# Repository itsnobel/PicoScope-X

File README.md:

# PicoScope-X
**PicoScope-X** is a compact, handheld, lightweight and portable powerful oscilloscope powered by Raspberry Pi Pico 2 (RP2350). It has 4-channel logic analyzer. This build features auto-ranging analog front-end (AFE), real-time power monitoring, a 3.2" TFT display to show outputs in sine waves, rectangles or triangles according to which signal we'll measure. Also onboard micro-SD data logging can help to sort out all data.
## Features

* **Dual-Channel Oscilloscope:** Runs on RB2350's dual core processing power to actively measure the waves formed by buffering sine wave, rectangle or triangle signal like a oscilloscope using high-speed ADCs (ADC0/ADC1). 
* **4-Channel Logic Analyzer:**  Digital signal capture utilizing RP2350 PIO (PIO0) for debugging SPI, I2C, UART, and GPIO states.
* **Auto-Ranging Input (1x / 10x(can be upgraded to 100x):** DG419 analog switches automaticly switch between direct input and a precision resistor divider network for high range voltage measurements.
* **Real-Time Power & Battery Monitor:** Integrated INA219 sensor tracks live current, voltage, and power consumption, and battery capacity (mAh) discharge testing.
* **Interactive UI & Storage:** Dual rotary encoders for seamless menu navigation, timebase/voltage scaling, and a Micro-SD card slot for saving screenshots and waveform data logs.
* **Power Management:** Powered by a 3.7V Li-Po battery with slide-switch control and diode for battery protection and charging while switch is off.

## Photos
The schematic like like mess as There were too many pins
---

---
The PCB designs are kinda cool. Looks like professional design.
---

---

## Repository Structure
PicoScope-X
├── PCB/              # EasyEDA schematic files, PCB layout, and gerbers
├── firmware/         # C++/MicroPython source code for RP2350
├── docs/             # Datasheets, pinout diagrams, and testing logs
└── README.md         # Project documentation

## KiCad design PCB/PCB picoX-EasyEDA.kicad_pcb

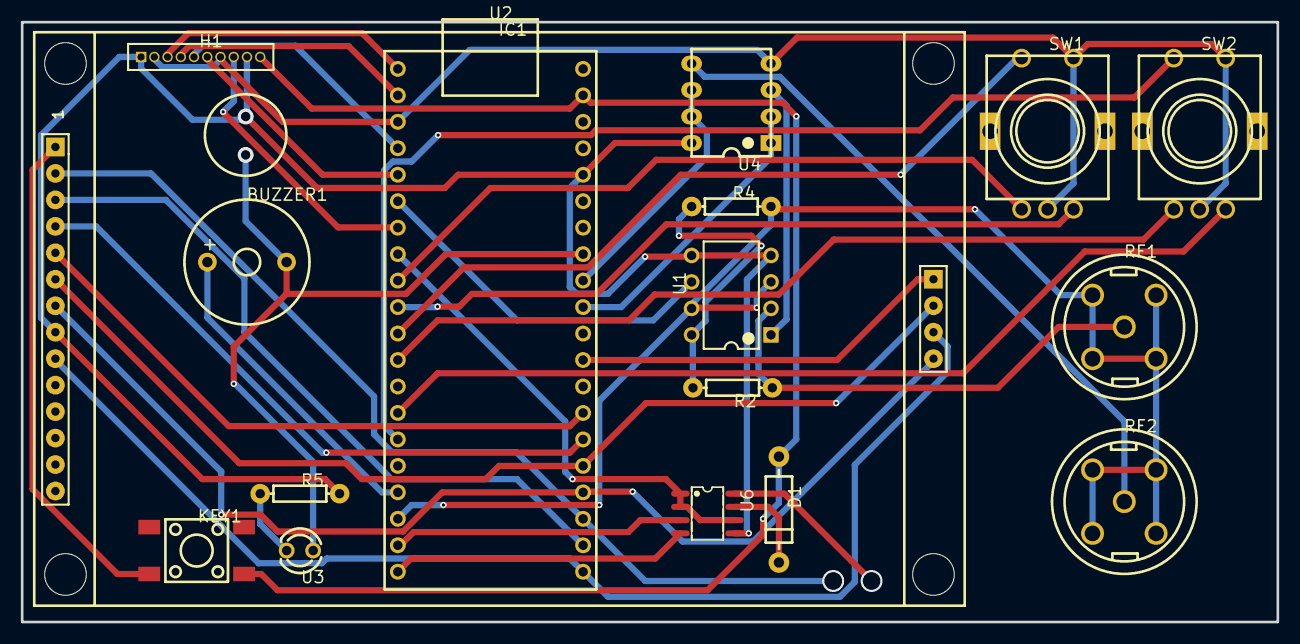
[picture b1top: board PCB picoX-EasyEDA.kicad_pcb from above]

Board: 2 copper layers, 120.5 x 57.6 mm, 17 parts (0 on the bottom side), 38 nets.

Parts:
BUZZER1: BUZZER-12X9; BUZ-TH_BD12.0-P7.60-D0.6-FD
D1: DIODE; DIODE-1N4001
H1: 1.27mm1*10P Straight Headers Pins; HDR-TH_10P-P1.27-V-M-1
IC1: TFT 3.2SPIA; TFT 3.2SPIM
KEY1: PUSHBUTTON; SW-SMD_4P-L6.0-W6.0-P4.50-LS10.0_TL3301EF160QG
R2, R4, R5: 1k; AXIAL-0.3
RF1, RF2: HL2-BNC-JE; BNC-TH_HL2-BNC-JE
SW1, SW2: Rotary switch; SW7-13.75X11.7X6.5MM
U1: DG419; DIP-8_L11.0-W7.6-P2.54-LS7.6-BL
U2: COLOREASYPICO2-RP2350; COMM-TH_COLOREASYPICO2-RP2350
U3: LED-2; LED-TH_BD3.0-P2.54-FD
U4: IC BAN TL072; TL072
U6: INA219BID; SOIC-8_L4.9-W3.9-P1.27-LS6.0-BL

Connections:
IC1_1: IC1.1, KEY1.3
U1_1: U1.1, U4.3
U1_2: R2.1, RF1.5, U1.2
U1_4: H1.1, H1.9, IC1.8, R5.2, U1.4, U1.5, U2.36, U4.8, U6.5
U1_6: U1.6, U2.6
U1_7: R4.2, RF1.1, RF1.2, RF1.3, RF1.4, RF2.1, RF2.2, RF2.3, RF2.4, U1.3, U1.7, U2.18
U1_8: R2.2, R4.1, U1.8
U2_1: H1.3, U2.1
U2_2: H1.4, U2.2
U2_3: H1.2, H1.7, SW1.2, SW1.4, SW2.2, SW2.4, U2.3, U4.4
U2_4: H1.5, U2.4
U2_5: H1.6, U2.5
U2_7: H1.8, U2.7
U2_8: U2.8, U6.1, U6.2, U6.6
U2_9: SW1.1, U2.9
U2_10: SW1.3, U2.10
U2_11: SW1.5, U2.11
U2_12: SW2.1, U2.12
U2_14: SW2.3, U2.14
U2_15: SW2.5, U2.15
U2_17: BUZZER1.1, U2.17
U2_19: U2.19, U6.3
U2_20: U2.20, U6.4
U2_21: IC1.9, IC1.17, U2.21
U2_22: IC1.3, U2.22
U2_23: IC1.2, U2.23
U2_24: IC1.7, IC1.18, U2.24
U2_25: IC1.6, IC1.16, U2.25
U2_26: IC1.4, U2.26
U2_27: IC1.5, U2.27
U2_29: IC1.15, U2.29
U2_31: U2.31, U4.1, U4.2
U2_32: U2.32, U4.6, U4.7
U2_33: BUZZER1.2, U2.33, U3.1
U2_39: D1.A, H1.10, KEY1.4, U2.39
U3_2: R5.1, U3.2
U4_5: RF2.5, U4.5
U6_7: D1.C, U6.7
